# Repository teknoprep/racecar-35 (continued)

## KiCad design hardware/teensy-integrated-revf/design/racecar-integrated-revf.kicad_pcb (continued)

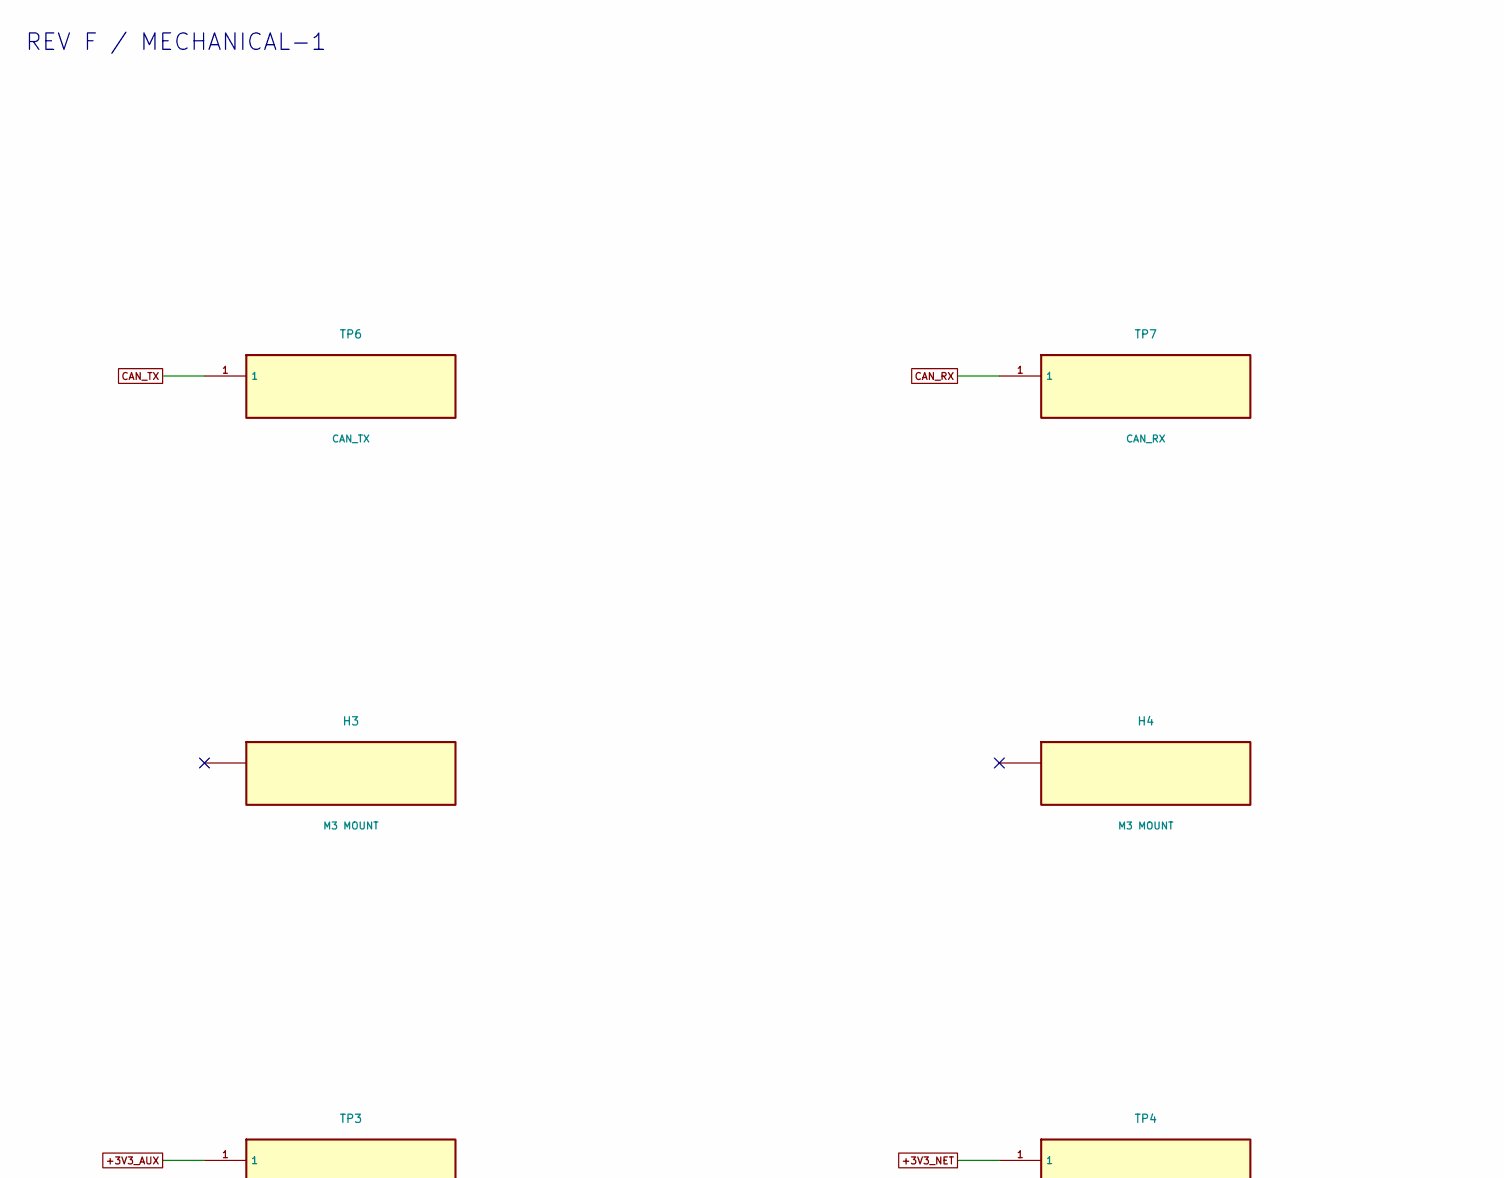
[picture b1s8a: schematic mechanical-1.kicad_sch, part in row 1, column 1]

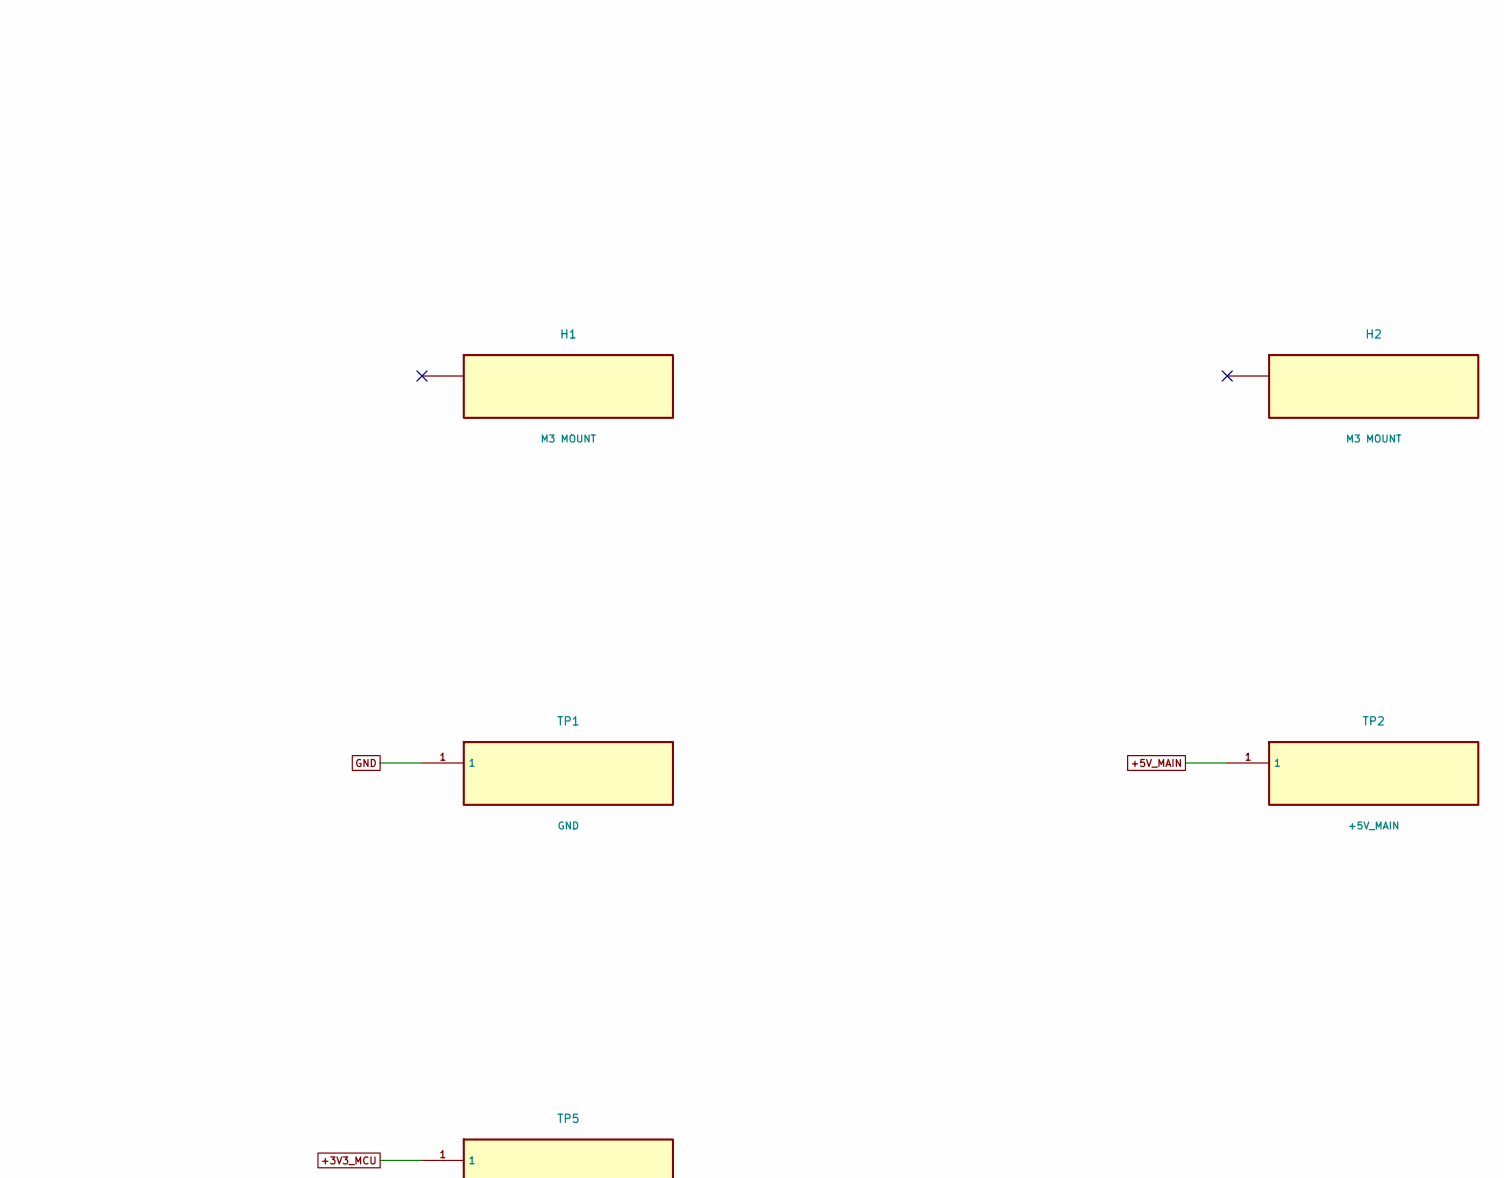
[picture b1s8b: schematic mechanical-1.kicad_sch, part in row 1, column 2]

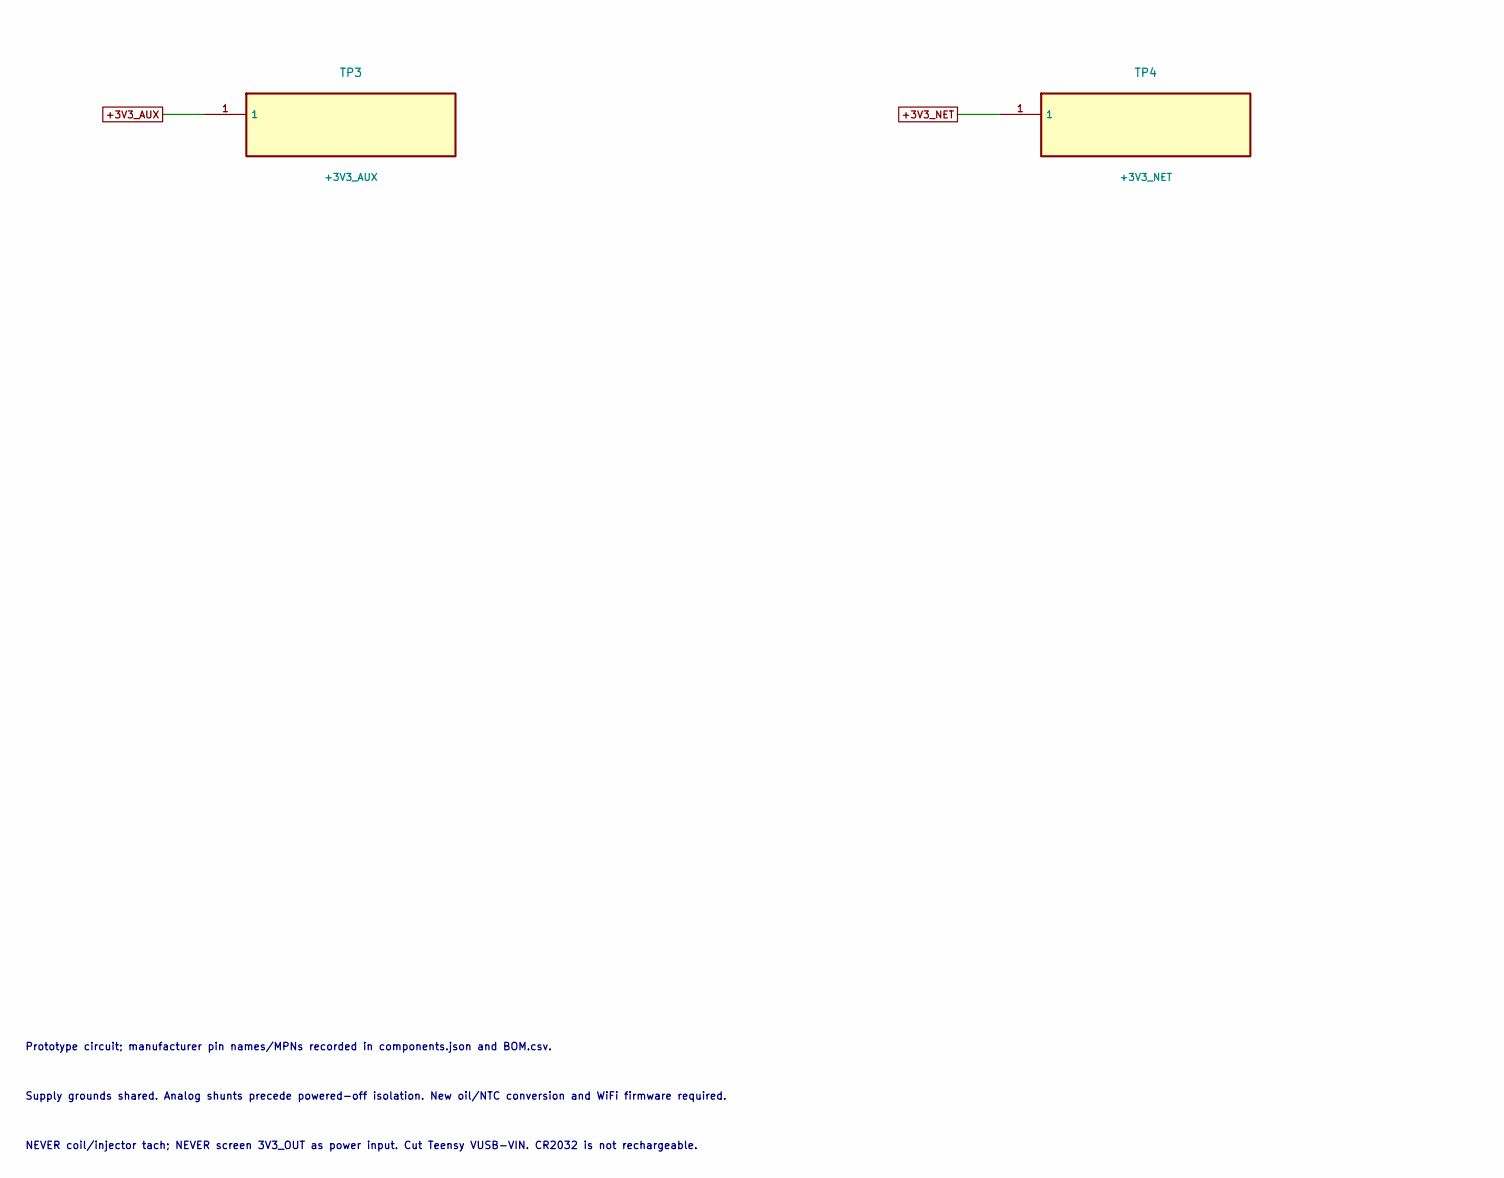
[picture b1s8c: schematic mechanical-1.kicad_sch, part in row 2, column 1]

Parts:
H1, H2, H3, H4: M3 MOUNT; MountingHole_3.2mm_M3
TP1: GND; TestPoint_THTPad_D2.0mm_Drill1.0mm
TP2: +5V_MAIN; TestPoint_THTPad_D2.0mm_Drill1.0mm
TP3: +3V3_AUX; TestPoint_THTPad_D2.0mm_Drill1.0mm
TP4: +3V3_NET; TestPoint_THTPad_D2.0mm_Drill1.0mm
TP5: +3V3_MCU; TestPoint_THTPad_D2.0mm_Drill1.0mm
TP6: CAN_TX; TestPoint_THTPad_D2.0mm_Drill1.0mm
TP7: CAN_RX; TestPoint_THTPad_D2.0mm_Drill1.0mm

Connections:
+3V3_AUX: TP3.1; also elsewhere on the board
+3V3_MCU: TP5.1; also elsewhere on the board
+3V3_NET: TP4.1; also elsewhere on the board
+5V_MAIN: TP2.1; also elsewhere on the board
CAN_RX: TP7.1; also elsewhere on the board
CAN_TX: TP6.1; also elsewhere on the board
GND: TP1.1; also elsewhere on the board

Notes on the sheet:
REV F / MECHANICAL-1
Prototype circuit; manufacturer pin names/MPNs recorded in components.json and BOM.csv.
Supply grounds shared. Analog shunts precede powered-off isolation. New oil/NTC conversion and WiFi firmware required.
NEVER coil/injector tach; NEVER screen 3V3_OUT as power input. Cut Teensy VUSB-VIN. CR2032 is not rechargeable.

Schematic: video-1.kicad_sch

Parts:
D3, D4: UART ESD; D_SOD-323
J13: PI 5 VIDEO 3V3 UART; JST_XH_B4B-XH-A_1x04_P2.50mm_Vertical
R1, R2: 1k 1%; R_0805_2012Metric

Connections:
GND: D3.2, D4.2, J13.1 (GND), J13.4 (GND); also elsewhere on the board
VID_RX_CABLE: D4.1, J13.3 (RX from Pi), R2.1
VID_RX_MCU: R2.2; also elsewhere on the board
VID_TX_CABLE: D3.1, J13.2 (TX to Pi), R1.2
VID_TX_MCU: R1.1; also elsewhere on the board

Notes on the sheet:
REV F / VIDEO-1
Prototype circuit; manufacturer pin names/MPNs recorded in components.json and BOM.csv.
Supply grounds shared. Analog shunts precede powered-off isolation. New oil/NTC conversion and WiFi firmware required.
NEVER coil/injector tach; NEVER screen 3V3_OUT as power input. Cut Teensy VUSB-VIN. CR2032 is not rechargeable.

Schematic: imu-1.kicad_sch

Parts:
C9: 100n; C_0805_2012Metric
C10: 10n; C_0805_2012Metric
C11: 2.2u; C_0805_2012Metric
R3, R4: 10k 1%; R_0805_2012Metric
U7: ICM-42670-P; InvenSense_LGA-14_2.5x3.0mm_P0.50mm

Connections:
+3V3_MCU: C9.1, C10.1, C11.1, R3.1, R4.1, U7.5 (VDDIO), U7.8 (VDD), U7.12 (AP_CS); also elsewhere on the board
GND: C9.2, C10.2, C11.2, U7.1 (AP_SDO/AP_AD0), U7.2 (RESV), U7.3 (RESV), U7.6 (GND), U7.7 (FSYNC), U7.10 (RESV), U7.11 (RESV); also elsewhere on the board
IMU_SCL: R4.2, U7.13 (AP_SCL); also elsewhere on the board
IMU_SDA: R3.2, U7.14 (AP_SDA); also elsewhere on the board

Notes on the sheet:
REV F / IMU-1
Prototype circuit; manufacturer pin names/MPNs recorded in components.json and BOM.csv.
Supply grounds shared. Analog shunts precede powered-off isolation. New oil/NTC conversion and WiFi firmware required.
NEVER coil/injector tach; NEVER screen 3V3_OUT as power input. Cut Teensy VUSB-VIN. CR2032 is not rechargeable.

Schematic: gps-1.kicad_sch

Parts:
C12, C15, C16, C17: 100n; C_0805_2012Metric
C13: 10u; C_0805_2012Metric
C14: 100pF C0G; C_0402_1005Metric
D5: RF ESD; D_SOD-882
J8: GPS SMA FEMALE; SMA_Amphenol_901-143_Horizontal
L1: 27nH RF choke; L_0402_1005Metric
R5: 10R 1%; R_0805_2012Metric
U8: NEO-M9N-00B; ublox_NEO
U9: TPS2553; SOT-23-6
U10: SN74LVC1G125; SOT-23-5

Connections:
+3V3_AUX: C12.1, C13.1, C15.1, C17.1, U8.2 (D_SEL), U8.22 (V_BCKP), U8.23 (VCC), U9.1 (IN), U9.3 (EN), U9.5 (ILIM), U10.5 (VCC); also elsewhere on the board
ANT_BIAS: C16.1, L1.2, R5.2
ANT_SWITCH: R5.1, U9.6 (OUT)
GND: C12.2, C13.2, C15.2, C16.2, C17.2, D5.2, J8.2, U8.4 (EXTINT), U8.7 (V_USB), U8.10 (GND), U8.12 (GND), U8.13 (GND), U8.24 (GND), U9.2 (GND), U10.1 (OE_N), U10.3 (GND); also elsewhere on the board
GPS_RX_AUX: U8.21 (RXD), U10.4 (Y)
GPS_TX_AUX: U8.20 (TXD); also elsewhere on the board
GPS_TX_MCU: U10.2 (A); also elsewhere on the board
RF_ANT: C14.1, D5.1, J8.1, L1.1
RF_GNSS: C14.2, U8.11 (RF_IN)

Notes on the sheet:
REV F / GPS-1
Prototype circuit; manufacturer pin names/MPNs recorded in components.json and BOM.csv.
Supply grounds shared. Analog shunts precede powered-off isolation. New oil/NTC conversion and WiFi firmware required.
NEVER coil/injector tach; NEVER screen 3V3_OUT as power input. Cut Teensy VUSB-VIN. CR2032 is not rechargeable.

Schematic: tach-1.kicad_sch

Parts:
C18: 1n; C_0805_2012Metric
C19, C20: 100n; C_0805_2012Metric
D6: LM4040 2.5; SOT-23
D7: PMEG2010ER; Nexperia_CFP3_SOD-123W
J3: TACH INPUT; TerminalBlock_Phoenix_MKDS-1,5-2-5.08_1x02_P5.08mm_Horizont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
Q1: MMBT3904; SOT-23
R6: 180k 1%; R_0805_2012Metric
R7: 22k 1%; R_0805_2012Metric
R8: 240k 1%; R_0805_2012Metric
R9, R12: 10k 1%; R_0805_2012Metric
R10: 2.2M 1%; R_0805_2012Metric
R11: 4.7k 1%; R_0805_2012Metric
R13: 100k 1%; R_0805_2012Metric
U11: LM2903B; SOIC-8_3.9x4.9mm_P1.27mm

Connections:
+5V_MAIN: C20.1, R8.1, R11.1, U11.8 (VCC); also elsewhere on the board
GND: C18.2, C19.2, C20.2, D6.2 (A), D6.3 (A/NC), D7.2 (A), J3.2 (RETURN), Q1.2 (E), R7.2, R9.2, R13.2, U11.4 (GND), U11.5 (IN2+); also elsewhere on the board
TACH_BASE: Q1.1 (B), R12.2, R13.1
TACH_CMP: R10.1, R11.2, R12.1, U11.1 (OUT1)
TACH_IN: J3.1 (SIGNAL), R6.1
TACH_LED_K: Q1.3 (C); also elsewhere on the board
TACH_REF: C19.1, R8.2, R9.1, U11.2 (IN1-), U11.6 (IN2-)
TACH_SENSE: C18.1, D6.1 (K), D7.1 (K), R6.2, R7.1, R10.2, U11.3 (IN1+)

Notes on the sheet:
REV F / TACH-1
Prototype circuit; manufacturer pin names/MPNs recorded in components.json and BOM.csv.
Supply grounds shared. Analog shunts precede powered-off isolation. New oil/NTC conversion and WiFi firmware required.
NEVER coil/injector tach; NEVER screen 3V3_OUT as power input. Cut Teensy VUSB-VIN. CR2032 is not rechargeable.

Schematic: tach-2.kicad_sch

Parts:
C21: 100n; C_0805_2012Metric
R14: 680 1%; R_0805_2012Metric
R15: 4.7k 1%; R_0805_2012Metric
U12: VO617A-3; SMDIP-4_W9.53mm
U13: SN74LVC2G17; SOT-23-6

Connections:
+3V3_MCU: C21.1, R15.1, U13.5 (VCC); also elsewhere on the board
+5V_MAIN: R14.1; also elsewhere on the board
GND: C21.2, U12.3 (E), U13.2 (GND); also elsewhere on the board
GPS_RX_MCU: U13.4 (2Y); also elsewhere on the board
GPS_TX_AUX: U13.3 (2A); also elsewhere on the board
TACH_LED_A: R14.2, U12.1 (LED A)
TACH_LED_K: U12.2 (LED K); also elsewhere on the board
TACH_MCU: U13.6 (1Y); also elsewhere on the board
TACH_OPTO: R15.2, U12.4 (C), U13.1 (1A)

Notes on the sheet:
REV F / TACH-2
Prototype circuit; manufacturer pin names/MPNs recorded in components.json and BOM.csv.
Supply grounds shared. Analog shunts precede powered-off isolation. New oil/NTC conversion and WiFi firmware required.
NEVER coil/injector tach; NEVER screen 3V3_OUT as power input. Cut Teensy VUSB-VIN. CR2032 is not rechargeable.

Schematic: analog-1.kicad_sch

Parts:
C22: 100n; C_0805_2012Metric
D8: LM4040 3.0; SOT-23
D9: PMEG2010ER; Nexperia_CFP3_SOD-123W
F3, F4, F5: 100mA PTC; Fuse_1206_3216Metric
J4: OIL 0.5-4.5V; TerminalBlock_Phoenix_MKDS-1,5-3-5.08_1x03_P5.08mm_Horizont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
J5: COOLANT NTC; TerminalBlock_Phoenix_MKDS-1,5-2-5.08_1x02_P5.08mm_Horizont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
J6: AEM 30-0300 ONLY; TerminalBlock_Phoenix_MKDS-1,5-2-5.08_1x02_P5.08mm_Horizont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
J11: THROTTLE 0.5-4.5V; TerminalBlock_Phoenix_MKDS-1,5-3-5.08_1x03_P5.08mm_Horizont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
J12: BRAKE 0.5-4.5V; TerminalBlock_Phoenix_MKDS-1,5-3-5.08_1x03_P5.08mm_Horizont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
R16, R17, R19, R20: 20k 0.1%; R_0805_2012Metric
R18: 1k 1%; R_0805_2012Metric

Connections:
+5V_BRK: F5.2, J12.1 (5V OUT)
+5V_MAIN: F3.1, F4.1, F5.1; also elsewhere on the board
+5V_SENSOR: F3.2, J4.1 (5V OUT)
+5V_TPS: F4.2, J11.1 (5V OUT)
AFR_CLAMP: R19.2, R20.1; also elsewhere on the board
AFR_SIGNAL: J6.1 (WHITE SIG+), R19.1
BRK_SIGNAL: J12.3 (SIGNAL); also elsewhere on the board
GND: C22.2, D8.2 (A), D8.3 (A/NC), D9.2 (A), J4.2 (RETURN), J5.2 (RETURN), J6.2 (BROWN RETURN), J11.2 (RETURN), J12.2 (RETURN), R17.2, R20.2; also elsewhere on the board
NTC_SIGNAL: J5.1 (NTC); also elsewhere on the board
OIL_CLAMP: D8.1 (K), D9.1 (K), R16.2, R17.1, R18.1
OIL_FILTER: C22.1, R18.2; also elsewhere on the board
OIL_SIGNAL: J4.3 (SIGNAL), R16.1
TPS_SIGNAL: J11.3 (SIGNAL); also elsewhere on the board

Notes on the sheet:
REV F / ANALOG-1
Prototype circuit; manufacturer pin names/MPNs recorded in components.json and BOM.csv.
Supply grounds shared. Analog shunts precede powered-off isolation. New oil/NTC conversion and WiFi firmware required.
NEVER coil/injector tach; NEVER screen 3V3_OUT as power input. Cut Teensy VUSB-VIN. CR2032 is not rechargeable.

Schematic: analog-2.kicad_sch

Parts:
C23, C24, C25: 100n; C_0805_2012Metric
D10, D12, D14: LM4040 3.0; SOT-23
D11, D13, D15: PMEG2010ER; Nexperia_CFP3_SOD-123W
R21, R24, R27: 1k 1%; R_0805_2012Metric
R22, R23, R25, R26: 20k 0.1%; R_0805_2012Metric

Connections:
AFR_CLAMP: D10.1 (K), D11.1 (K), R21.1; also elsewhere on the board
AFR_FILTER: C23.1, R21.2; also elsewhere on the board
GND: C23.2, C24.2, C25.2, D10.2 (A), D10.3 (A/NC), D11.2 (A), D12.2 (A), D12.3 (A/NC), D13.2 (A), D14.2 (A), D14.3 (A/NC), D15.2 (A), R23.2, R26.2; also elsewhere on the board
NTC_CLAMP: D12.1 (K), D13.1 (K), R22.2, R23.1, R24.1
NTC_FILTER: C24.1, R24.2; also elsewhere on the board
NTC_SIGNAL: R22.1; also elsewhere on the board
TPS_CLAMP: D14.1 (K), D15.1 (K), R25.2, R26.1, R27.1
TPS_FILTER: C25.1, R27.2; also elsewhere on the board
TPS_SIGNAL: R25.1; also elsewhere on the board

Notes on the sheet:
REV F / ANALOG-2
Prototype circuit; manufacturer pin names/MPNs recorded in components.json and BOM.csv.
Supply grounds shared. Analog shunts precede powered-off isolation. New oil/NTC conversion and WiFi firmware required.
NEVER coil/injector tach; NEVER screen 3V3_OUT as power input. Cut Teensy VUSB-VIN. CR2032 is not rechargeable.

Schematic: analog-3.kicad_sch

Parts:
C26, C27, C40: 100n; C_0805_2012Metric
D16, D21: LM4040 3.0; SOT-23
D17, D18, D22: PMEG2010ER; Nexperia_CFP3_SOD-123W
R28, R29, R49: 20k 0.1%; R_0805_2012Metric
R30, R50: 1k 1%; R_0805_2012Metric
R31: 150 1%; R_0805_2012Metric
R48: 180k 0.1%; R_0805_2012Metric
U14: LM4040 4.1; SOT-23

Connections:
+5V_MAIN: D18.2 (A); also elsewhere on the board
BRK_CLAMP: D16.1 (K), D17.1 (K), R28.2, R29.1, R30.1
BRK_FILTER: C26.1, R30.2; also elsewhere on the board
BRK_SIGNAL: R28.1; also elsewhere on the board
GND: C26.2, C27.2, C40.2, D16.2 (A), D16.3 (A/NC), D17.2 (A), D21.2 (A), D21.3 (A/NC), D22.2 (A), R29.2, R49.2, U14.2 (A), U14.3 (A/NC); also elsewhere on the board
NTC_EXC: C27.1, R31.2, U14.1 (K); also elsewhere on the board
NTC_FEED: D18.1 (K), R31.1
VINMON_CLAMP: D21.1 (K), D22.1 (K), R48.2, R49.1, R50.1
VINMON_FILTER: C40.1, R50.2; also elsewhere on the board
VIN_FUSED: R48.1; also elsewhere on the board

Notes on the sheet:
REV F / ANALOG-3
Prototype circuit; manufacturer pin names/MPNs recorded in components.json and BOM.csv.
Supply grounds shared. Analog shunts precede powered-off isolation. New oil/NTC conversion and WiFi firmware required.
NEVER coil/injector tach; NEVER screen 3V3_OUT as power input. Cut Teensy VUSB-VIN. CR2032 is not rechargeable.

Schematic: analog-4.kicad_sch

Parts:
C28, C29: 100n; C_0805_2012Metric
R32: 2.49k 0.1%; R_0805_2012Metric
U15, U16: TMUX1511; TSSOP-14_4.4x5mm_P0.65mm

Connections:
+3V3_MCU: C28.1, C29.1, U15.1 (SEL1), U15.4 (SEL2), U15.10 (SEL3), U15.13 (SEL4), U15.14 (VDD), U16.1 (SEL1), U16.4 (SEL2), U16.14 (VDD); also elsewhere on the board
AFR_ADC: U15.6 (D2); also elsewhere on the board
AFR_FILTER: U15.5 (S2); also elsewhere on the board
BRK_ADC: U16.6 (D2); also elsewhere on the board
BRK_FILTER: U16.5 (S2); also elsewhere on the board
GND: C28.2, C29.2, U15.7 (GND), U16.7 (GND), U16.12 (S4), U16.13 (SEL4); also elsewhere on the board
NTC_ADC: U15.8 (D3); also elsewhere on the board
NTC_EXC: R32.1; also elsewhere on the board
NTC_FILTER: U15.9 (S3); also elsewhere on the board
NTC_SIGNAL: R32.2; also elsewhere on the board
OIL_ADC: U15.3 (D1); also elsewhere on the board
OIL_FILTER: U15.2 (S1); also elsewhere on the board
TPS_ADC: U16.3 (D1); also elsewhere on the board
TPS_FILTER: U16.2 (S1); also elsewhere on the board
VINMON_ADC: U15.11 (D4); also elsewhere on the board
VINMON_FILTER: U15.12 (S4); also elsewhere on the board

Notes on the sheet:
REV F / ANALOG-4
Prototype circuit; manufacturer pin names/MPNs recorded in components.json and BOM.csv.
Supply grounds shared. Analog shunts precede powered-off isolation. New oil/NTC conversion and WiFi firmware required.
NEVER coil/injector tach; NEVER screen 3V3_OUT as power input. Cut Teensy VUSB-VIN. CR2032 is not rechargeable.

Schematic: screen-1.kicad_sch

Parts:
C30, C31, C32, C33: 100n; C_0805_2012Metric
D19, D20: UART ESD; D_SOD-323
J2: SCREEN J10 ONLY; TerminalBlock_Phoenix_MKDS-1,5-4-5.08_1x04_P5.08mm_Horizont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
R33, R34: 100 1%; R_0805_2012Metric
R35, R36: 47k 1%; R_0805_2012Metric
U4, U5: SN74LVC1T45; SOT-23-6

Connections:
+3V3_MCU: C30.1, C32.1, R35.1, U4.1 (VCCA), U4.5 (DIR), U5.1 (VCCA); also elsewhere on the board
+5V_SCREEN: C31.1, C33.1, J2.2 (5V OUT), R36.1, U4.6 (VCCB), U5.6 (VCCB); also elsewhere on the board
DASH_RX_5V: R34.2, U5.4 (B)
DASH_RX_CABLE: D20.1, J2.3 (RX FROM), R34.1, R36.2
DASH_RX_MCU: U5.3 (A); also elsewhere on the board
DASH_TX_5V: R33.1, U4.4 (B)
DASH_TX_CABLE: D19.1, J2.4 (TX TO), R33.2
DASH_TX_MCU: R35.2, U4.3 (A); also elsewhere on the board
GND: C30.2, C31.2, C32.2, C33.2, D19.2, D20.2, J2.1 (GND), U4.2 (GND), U5.2 (GND), U5.5 (DIR); also elsewhere on the board

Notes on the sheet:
REV F / SCREEN-1
Prototype circuit; manufacturer pin names/MPNs recorded in components.json and BOM.csv.
Supply grounds shared. Analog shunts precede powered-off isolation. New oil/NTC conversion and WiFi firmware required.
NEVER coil/injector tach; NEVER screen 3V3_OUT as power input. Cut Teensy VUSB-VIN. CR2032 is not rechargeable.

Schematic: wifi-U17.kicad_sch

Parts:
U17: ESP32-S3-WROOM-1-N8R2; ESP32-S3-WROOM-1

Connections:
+3V3_NET: U17.2 (3V3); also elsewhere on the board
GND: U17.1 (GND), U17.40 (GND), U17.41 (EP GND); also elsewhere on the board
NET_BOOT: U17.27 (GPIO0 BOOT); also elsewhere on the board
NET_CS: U17.18 (GPIO10 CS); also elsewhere on the board
NET_EN: U17.3 (EN); also elsewhere on the board
NET_IRQ: U17.22 (GPIO14 IRQ); also elsewhere on the board
NET_MISO: U17.21 (GPIO13 MISO); also elsewhere on the board
NET_MOSI: U17.19 (GPIO11 MOSI); also elsewhere on the board
NET_SCK: U17.20 (GPIO12 SCK); also elsewhere on the board
NET_UART_RX: U17.36 (GPIO44 RXD0); also elsewhere on the board
NET_UART_TX: U17.37 (GPIO43 TXD0); also elsewhere on the board

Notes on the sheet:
REV F / WIFI-U17
Prototype circuit; manufacturer pin names/MPNs recorded in components.json and BOM.csv.
Supply grounds shared. Analog shunts precede powered-off isolation. New oil/NTC conversion and WiFi firmware required.
NEVER coil/injector tach; NEVER screen 3V3_OUT as power input. Cut Teensy VUSB-VIN. CR2032 is not rechargeable.

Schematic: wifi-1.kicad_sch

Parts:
C34: 10u; C_0805_2012Metric
C35, C37: 100n; C_0805_2012Metric
C36: 1u; C_0805_2012Metric
Q2: MMBT3904; SOT-23
R37, R38, R39, R44: 10k 1%; R_0805_2012Metric
R40: 100k 1%; R_0805_2012Metric
R41, R42, R43: 33 1%; R_0805_2012Metric
R45: 47k 1%; R_0805_2012Metric
U18: SN74LVC125A; TSSOP-14_4.4x5mm_P0.65mm
U19: SN74LVC2G125; VSSOP-8_2.3x2mm_P0.5mm

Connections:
+3V3_MCU: R44.1, U19.8 (VCC); also elsewhere on the board
+3V3_NET: C34.1, C35.1, C37.1, R37.1, R38.1, U18.13 (4OE_N), U18.14 (VCC); also elsewhere on the board
GND: C34.2, C35.2, C36.2, C37.2, Q2.2 (E), R40.2, R45.2, U18.1 (1OE_N), U18.4 (2OE_N), U18.7 (GND), U18.10 (3OE_N), U18.12 (4A), U19.1 (1OE_N), U19.4 (GND), U19.7 (2OE_N); also elsewhere on the board
NET_BOOT: R38.2; also elsewhere on the board
NET_CS: R41.2; also elsewhere on the board
NET_CS_MCU: R44.2, U18.2 (1A); also elsewhere on the board
NET_CS_PRE: R41.1, U18.3 (1Y)
NET_EN: C36.1, Q2.3 (C), R37.2; also elsewhere on the board
NET_IRQ: U19.6 (2A); also elsewhere on the board
NET_IRQ_MCU: U19.5 (2Y); also elsewhere on the board
NET_MISO: U19.2 (1A); also elsewhere on the board
NET_MISO_MCU: U19.3 (1Y); also elsewhere on the board
NET_MOSI: R42.2; also elsewhere on the board
NET_MOSI_MCU: U18.5 (2A); also elsewhere on the board
NET_MOSI_PRE: R42.1, U18.6 (2Y)
NET_RESET_ASSERT: R39.1; also elsewhere on the board
NET_RESET_BASE: Q2.1 (B), R39.2, R40.1
NET_SCK: R43.2; also elsewhere on the board
NET_SCK_MCU: R45.1, U18.9 (3A); also elsewhere on the board
NET_SCK_PRE: R43.1, U18.8 (3Y)

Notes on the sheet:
REV F / WIFI-1
Prototype circuit; manufacturer pin names/MPNs recorded in components.json and BOM.csv.
Supply grounds shared. Analog shunts precede powered-off isolation. New oil/NTC conversion and WiFi firmware required.
NEVER coil/injector tach; NEVER screen 3V3_OUT as power input. Cut Teensy VUSB-VIN. CR2032 is not rechargeable.

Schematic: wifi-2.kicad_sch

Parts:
C38, C39: 100n; C_0805_2012Metric
J10: NET 3V3 UART SERVICE; PinHeader_2x03_P2.54mm_Vertical
R46, R47: 47k 1%; R_0805_2012Metric
U20: SN74LVC1G125; SOT-23-5

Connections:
+3V3_MCU: C38.1; also elsewhere on the board
+3V3_NET: C39.1, J10.2, U20.5; also elsewhere on the board
GND: C38.2, C39.2, J10.1, R46.2, R47.2, U20.1, U20.3; also elsewhere on the board
NET_BOOT: J10.5; also elsewhere on the board
NET_EN: J10.6; also elsewhere on the board
NET_IRQ: R46.1; also elsewhere on the board
NET_MISO: R47.1; also elsewhere on the board
NET_UART_EXT_RX: J10.4, U20.2
NET_UART_RX: U20.4; also elsewhere on the board
NET_UART_TX: J10.3; also elsewhere on the board

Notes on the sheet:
REV F / WIFI-2
Prototype circuit; manufacturer pin names/MPNs recorded in components.json and BOM.csv.
Supply grounds shared. Analog shunts precede powered-off isolation. New oil/NTC conversion and WiFi firmware required.
NEVER coil/injector tach; NEVER screen 3V3_OUT as power input. Cut Teensy VUSB-VIN. CR2032 is not rechargeable.

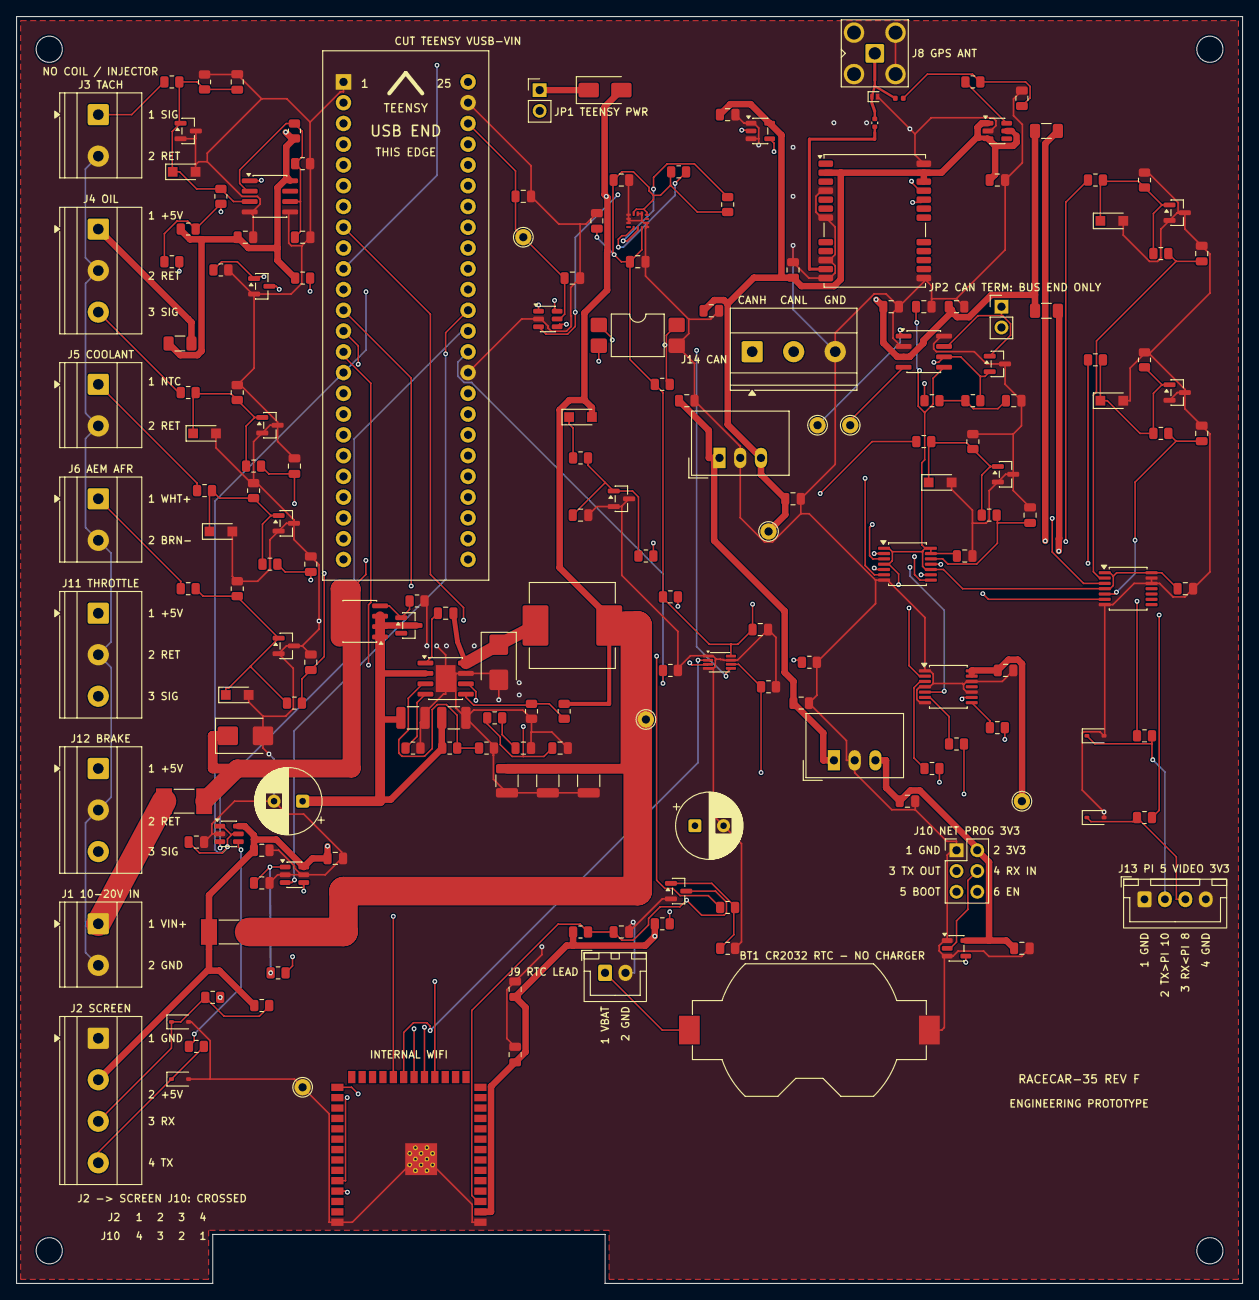
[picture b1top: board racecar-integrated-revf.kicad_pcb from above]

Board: 4 copper layers, 150.0 x 155.0 mm, 193 parts (0 on the bottom side), 103 nets.

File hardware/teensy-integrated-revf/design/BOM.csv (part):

Reference,Function,Value,Manufacturer,MPN,Footprint,Notes
Q3,Q_REV,AO4485 P-FET 40V,Alpha & Omega Semiconductor,AO4485,RacecarC:SOIC-8_3.9x4.9mm_P1.27mm,"Reverse-polarity protection: DRAIN=raw input, SOURCE=protected load so the body diode blocks a reversed supply. P-Channel, 40V, 15mOhm at Vgs=-10V. Vds 40V vs the 32V TVS clamp."
R51,R_REVG,10k 1%,Yageo,RC0805FR-0710KL,RacecarC:R_0805_2012Metric,0805; >=0.125W
D24,D_REVZ,BZX84C15,Nexperia,BZX84C15,RacecarC:SOT-23,"15V gate-source clamp for Q_REV: Vgs rating is +/-20V, the input can reach 32V."
C43,C_BOOT,100n,Murata,GRM21BR71H104KA01L,RacecarC:C_0805_2012Metric,"Bootstrap capacitor BOOT-SW, 50V rated for a 20V rail."
U2,U2,TPS54560B 5V 5A BUCK,Texas Instruments,TPS54560BDDAR,RacecarC:SOIC-8-1EP_3.9x4.9mm_P1.27mm_EP2.41x3.3mm,"60V 5A asynchronous buck at 400kHz, TI 5V/5A design example. PowerPAD (pad 9) is GND and carries the heat: thermal vias north and south of the pad, NOT inside it, so no via-in-pad resin fill is needed."
C41,C_IN1,10uF 50V X7R 1210,Murata,GRM32ER71H106KA12L,RacecarC:C_1210_3225Metric,"50V rating on a 10-20V rail; a 5A buck input needs ceramic close to the VIN pin, not only C1 bulk."
C42,C_IN2,10uF 50V X7R 1210,Murata,GRM32ER71H106KA12L,RacecarC:C_1210_3225Metric,"50V rating on a 10-20V rail; a 5A buck input needs ceramic close to the VIN pin, not only C1 bulk."
D23,D_MAIN,SS56 catch diode,BORN,SS56,RacecarC:D_SMB,"Asynchronous buck catch diode: 5A, 60V vs the 32V clamp. Carries the full inductor current during off-time. MUST be the SMB (DO-214AA) part - the bare SS56 is normally SMA (DO-214AC) and will not fit this D_SMB land pattern. LCSC C2687867 (BORN SS56, SMB) or Diotec SK56."
L2,L_MAIN,6.8uH 8A RMS SHIELDED,Vishay,IHLP4040DZER6R8M01,RacecarC:L_Vishay_IHLP-4040,"6.8uH, 23.3mOhm, 13.5A saturation / 8A RMS vs 5A DC and 5.7A peak. Lmin for 20V in / 400kHz / 5A is 6.25uH."
C44,C_OUT1,47uF 16V X5R 1210,Murata,GRM32ER61C476KE15L,RacecarC:C_1210_3225Metric,TI design example output capacitance (3x47uF); the compensation below assumes it.
C45,C_OUT2,47uF 16V X5R 1210,Murata,GRM32ER61C476KE15L,RacecarC:C_1210_3225Metric,TI design example output capacitance (3x47uF); the compensation below assumes it.
C46,C_OUT3,47uF 16V X5R 1210,Murata,GRM32ER61C476KE15L,RacecarC:C_1210_3225Metric,TI design example output capacitance (3x47uF); the compensation below assumes it.
R53,R_FBH,52.3k 0.1%,Yageo,RT0805BRD0752K3L,RacecarC:R_0805_2012Metric,Thin-film 0.1%
R54,R_FBL,10k 1%,Yageo,RC0805FR-0710KL,RacecarC:R_0805_2012Metric,0805; >=0.125W
R55,R_COMP,16.9k 1%,Yageo,RC0805FR-0716K9L,RacecarC:R_0805_2012Metric,0805; >=0.125W
C47,C_COMP,4.7n,Samsung,CL21B472KBANNNC,RacecarC:C_0805_2012Metric,Compensation zero at the modulator pole (TI 8.2.2.11).
C48,C_CPOLE,47p,Samsung,CL21C470JBANNNC,RacecarC:C_0805_2012Metric,High-frequency compensation pole.
R52,R_RT,240k 1%,Yageo,RC0805FR-07240KL,RacecarC:R_0805_2012Metric,0805; >=0.125W
R56,R_UV1,680k 1%,Yageo,RC0805FR-07680KL,RacecarC:R_0805_2012Metric,0805; >=0.125W
R57,R_UV2,100k 1%,Yageo,RC0805FR-07100KL,RacecarC:R_0805_2012Metric,0805; >=0.125W
U3,U3,TSR 1-2433,TRACO Power,TSR 1-2433,RacecarC:Converter_DCDC_TRACO_TSR-1_THT,"Separate 1A module fed by the protected rail (10-20V), NOT the marginal 5V input."
C3,C_U3I,100n,Murata,GRM21BR71H104KA01L,RacecarC:C_0805_2012Metric,X7R 50V; 10uF is X5R 25V
C4,C_U3O,10u,Murata,GRM21BR61E106KA73L,RacecarC:C_0805_2012Metric,X7R 50V; 10uF is X5R 25V
U6,U_NET_PWR,TSR 1-2433,TRACO Power,TSR 1-2433,RacecarC:Converter_DCDC_TRACO_TSR-1_THT,"Separate 1A module fed by the protected rail (10-20V), NOT the marginal 5V input."
C5,C_U_NET_PWRI,100n,Murata,GRM21BR71H104KA01L,RacecarC:C_0805_2012Metric,X7R 50V; 10uF is X5R 25V
C6,C_U_NET_PWRO,10u,Murata,GRM21BR61E106KA73L,RacecarC:C_0805_2012Metric,X7R 50V; 10uF is X5R 25V
J1,J1,POWER IN,Phoenix Contact,1729018,"RacecarC:TerminalBlock_Phoenix_MKDS-1,5-2-5.08_1x02_P5.08mm_Horizontal",
F1,F1,5A fuse,Littelfuse,0451005.MRL,RacecarC:Fuse_Littelfuse-NANO2-451_453,
F2,F2,3A fuse,Littelfuse,0451003.MRL,RacecarC:Fuse_Littelfuse-NANO2-451_453,
D1,D1,SMBJ20CA,Littelfuse,SMBJ20CA,RacecarC:D_SMB,Bidirectional TVS; NOT automotive load-dump qualification
C1,C1,100uF 50V,Panasonic,EEU-FR1H101,RacecarC:CP_Radial_D8.0mm_P3.50mm,
C2,C2,470uF 10V,Panasonic,EEU-FR1A471B,RacecarC:CP_Radial_D8.0mm_P3.50mm,
D2,D2,SS14,onsemi,SS14,RacecarC:D_SMA,BOM-REV1: onsemi is the orderable MPN (bare SS14 from Diodes Inc is not).
JP1,JP1,MCU POWER,Samtec,TSW-102-07-G-S,RacecarC:PinHeader_1x02_P2.54mm_Vertical,Fit shunt after unloaded rail tests; cut Teensy VUSB-VIN before dual-power use
U1,U1,Teensy 4.1 SOCKETED,PJRC,TEENSY41,RacecarC:Teensy41_Socket,CUT VUSB-VIN. Two 24-pin sockets. VBAT via separate removable 2-wire service lead to labelled Teensy VBAT/GND pads.
C7,C_MCU,100n,Murata,GRM21BR71H104KA01L,RacecarC:C_0805_2012Metric,X7R 50V; 10uF is X5R 25V
BT1,BT1,CR2032 HOLDER,Keystone,1058,RacecarC:BatteryHolder_Keystone_1058_1x2032,Fit Panasonic CR2032 AFTER reflow/cleaning. Primary cell: NO charging.
J9,J_BAT,TO TEENSY VBAT/GND,JST,B2B-XH-A(LF)(SN),RacecarC:JST_XH_B2B-XH-A_1x02_P2.50mm_Vertical,"Short removable lead: 1 to Teensy VBAT auxiliary pad, 2 GND. NEVER 3V3/ONOFF. Required assembly operation."
U21,U21,TCAN1042HGV-Q1,Texas Instruments,TCAN1042HGVDRQ1,RacecarC:SOIC-8_3.9x4.9mm_P1.27mm,"AEC-Q100 CAN transceiver, +/-70V bus fault protection, VIO=3.3V so RXD is 3.3V logic. STB (pin 8) is tied DIRECTLY to GND with no resistor: standby is receive-only (no ACK), the exact failure mode of the removed SN65HVD230 module. Acceptable alternates: TCAN1042VDRQ1, then NXP TJA1051T/3/1J (its pin 8 = S must also go to GND). Do NOT fit an SN65HVD230 (only -4/+16V bus fault) or any non-VIO TJA1051T/TJA1050 (5V RXD would damage the Teensy)."
C49,C_U21V,100n,Murata,GRM21BR71H104KA01L,RacecarC:C_0805_2012Metric,X7R 50V; 10uF is X5R 25V
C50,C_U21IO,100n,Murata,GRM21BR71H104KA01L,RacecarC:C_0805_2012Metric,X7R 50V; 10uF is X5R 25V
C51,C_U21B,1u,Murata,GRM21BR71H105KA12L,RacecarC:C_0805_2012Metric,X7R 50V; 10uF is X5R 25V
J14,J14,CAN,Phoenix Contact,1729021,"RacecarC:TerminalBlock_Phoenix_MKDS-1,5-3-5.08_1x03_P5.08mm_Horizontal","1 CANH, 2 CANL, 3 GND (signal-ground reference to the ECU). Fit the split-termination jumper JP2 ONLY when this board is an end of the CAN bus."
D25,D_U21TVS,NUP2105L,onsemi,NUP2105LT1G,RacecarC:SOT-23,"Dual bidirectional CAN bus protector at J14 (SOT-23). Alternates: Nexperia PESD2CAN,215 or TI ESD2CAN24DBZRQ1."
JP2,JP2,CAN TERM,Samtec,TSW-102-07-G-S,RacecarC:PinHeader_1x02_P2.54mm_Vertical,"CAN TERM jumper (Samtec TSW-102 + shunt, as JP1). FIT ONLY IF THIS BOARD IS A BUS END; remove the shunt on a mid-bus tap. Do not fit while the ECU end is already terminated at 120R."
R58,R_T1,60.4R 1%,Yageo,RC0805FR-0760R4L,RacecarC:R_0805_2012Metric,Split-termination upper leg. Two 60.4R in series = 120.8R across CANH/CANL.
R59,R_T2,60.4R 1%,Yageo,RC0805FR-0760R4L,RacecarC:R_0805_2012Metric,Split-termination lower leg.
C52,C_T,4.7n,Samsung,CL21B472KBANNNC,RacecarC:C_0805_2012Metric,Split-termination midpoint bypass to GND (50V X7R).
TP6,TP6,CAN_TX,PCB,PCB test pad,RacecarC:TestPoint_THTPad_D2.0mm_Drill1.0mm,
TP7,TP7,CAN_RX,PCB,PCB test pad,RacecarC:TestPoint_THTPad_D2.0mm_Drill1.0mm,
J13,J_VID,PI 5 VIDEO 3V3 UART,JST,B4B-XH-A(LF)(SN),RacecarC:JST_XH_B4B-XH-A_1x04_P2.50mm_Vertical,"Pi 5 UART 115200 8N1, 3.3V only. NO 5V/12V here. Cameras and USB storage stay on the Pi and are NOT powered by this board."
R1,R_VIDTX,1k 1%,Yageo,RC0805FR-071KL,RacecarC:R_0805_2012Metric,0805; >=0.125W
R2,R_VIDRX,1k 1%,Yageo,RC0805FR-071KL,RacecarC:R_0805_2012Metric,0805; >=0.125W
D3,D_VIDTX,UART ESD,Nexperia,"PESD5V0S1BA,115",RacecarC:D_SOD-323,
D4,D_VIDRX,UART ESD,Nexperia,"PESD5V0S1BA,115",RacecarC:D_SOD-323,
U7,U_IMU,ICM-42670-P,TDK InvenSense,ICM-42670-P,RacecarC:InvenSense_LGA-14_2.5x3.0mm_P0.50mm,Address 0x68 (AP_AD0=GND); AP_CS=VDDIO selects I2C. Polling only; INT1/INT2 unconnected. RESV pads grounded per DS-000451.
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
